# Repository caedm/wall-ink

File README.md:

# Introduction
Wall-ink was designed from the ground up to be a scalable, [secure](https://github.com/caedm/wall-ink/wiki/Device-security), and completely open solution to display conference room schedules at a university.  The product could, however, be developed to display other images for advertising, directions, staff directories, a weather station, retail pricing, etc.  Currently, the [wall-ink-server](https://github.com/caedm/wall-ink-server) can display schedules from the open source [Booked scheduler](https://www.bookedscheduler.com), any web published iCal file (Outlook / Exchange), and the Google Calendar API.  It can also [rotate through a collection of static images](https://github.com/caedm/wall-ink-server/wiki/Plugin-architecture#static-images-plugin).  With [additional development](https://github.com/caedm/wall-ink-server/wiki/Coding-a-new-plugin), other scheduler integrations or functions are possible.  The hardware simply displays whatever image it is given when it checks in with a wall-ink-server.  Development for putting images on the e-ink screen is made simpler by [allowing the image creation processing](https://github.com/caedm/wall-ink-server/wiki/Wall-ink-image-formats-and-image-handling) to occur on the server side, and not on the device.  Server-side image creation was a design choice for deploying a large fleet of these devices across mulitple buildings.  This way, changes can be made to what the devices are displaying without having to update firmware on dozens or hundreds of devices.  To date, we are aware of several other groups who have successfully written their own server-side software for wall-ink devices in various languages.  Links to other related wall-ink projects are found on the [additional wall ink projects](https://github.com/caedm/wall-ink/wiki/Additional-wall-ink-projects) page.

The original design parameters of this project were to display a room schedule electronically with no wires, at the cheapest possible price point.  No Ethernet, no power wires, in a low-cost footprint.  The resulting project has produced a AA powered WiFi E-ink device for under $100 (US), when parts are purchased in bulk, where the [batteries last a year or two](https://github.com/caedm/wall-ink/wiki/Circuit#batteries).  

The wall-ink project along with the [Wall-Ink-Server](https://github.com/caedm/wall-ink-server) includes everything necessary to build the entire e-ink display system. 

# Summary
The wall-ink project has several components:

* [Circuit and electronics](https://github.com/caedm/wall-ink/wiki/circuit), including Eagle schematic, PCB layout and gerber files
* List of necessary [parts](https://github.com/caedm/wall-ink/wiki/partslist) to build the project
* Arduino IDE [Firmware](https://github.com/caedm/wall-ink/wiki/firmware) for the ESP8266 microcontroller
* CAD files to 3D print the [Case](https://github.com/caedm/wall-ink/wiki/firmware)
* See the [Wall-Ink-Server](https://github.com/caedm/wall-ink-server) project for server side code

# FAQ

## What hardware does wall-ink run on and where do I get it?
The wall-ink project is a hardware, firmware, and software build.  To date, we are not aware of any off-the-shelf commercial products that will do everything that the [wall-ink device](https://github.com/caedm/wall-ink/wiki/7.5%22-Wall-ink-device) does.  There are plenty of ESP8266 devices out there, including ones that sleep, but the hardware as described here is specifically designed to run the wall-ink firmware, sleep, use very little power, fit in the supplied 3D printable case, and update a Waveshare e-ink screen.

## Can I hire you to make the hardware for me?
Due to conflict of interest policies at the University we work for, we are not available for hire to create hardware for you, or to customize software features for you.  That being said, we have uploaded all of the design files and code, and reasonable documentation to do it on your own.  Many people have created this project on their own with positive results.

## What is an ESP8266 and why did you choose that microprocessor?
The [ESP8266 by Espressif Systems](https://en.wikipedia.org/wiki/ESP8266) is similar to an Arduino, but has 10uA deep-sleep function and built-in WiFi with a full TCP/IP stack.  The ESP8266 is also low cost, and fully compatible with the Arduino IDE.  So for under $3, you get a microprocessor that is perfect for this project.

## Why e-ink?  Is it a touch display?
In order to run the device for over a year on a set of AA batteries, we needed to use the lowest power screen possible. Since e-ink screens can hold their image even with the power removed, this is by far the lowest power option out there.  To keep the cost down, the type of [E-ink screens](https://en.wikipedia.org/wiki/E-ink) we chose from Waveshare / Good Display does not have touch screen capability.

## What e-ink screens are supported?
The real limitation of screen resolution support is the RAM available on the esp8266.  Some server-side plugins like the static image plugin and the simple text plugin can handle any screen size dynamically.  Other plugins like the booked and google plugins that use the general scheduling functions are hard-coded for Waveshare 7.5" screens at 640x384 and Waveshare 4.2" screens at 400x300 pixels.  There is currently no support for color displays.  We believe that there would be insufficient memory to support the larger color screens using the current method that the firmware has been coded.  The color screens also take a significant amount of time to update, and the batteries would not last sufficiently long for our use-case, so we did not pursue this option.

## Why does a wall-ink device require a server?
Using a central server for controlling what is displayed on wall-ink devices was a design decision to ease the management of large numbers of devices.  If you only need to manage one e-ink device, running a server component might be overkill, but with dozens or hundreds of devices in the field, it is essential.  Tweaking what is being displayed on 100 or more screens can be done by changing a parameter on a website rather than updating firmware on dozens of devices across the enterprise.  Any wall-ink device pointed to a wall-ink-server can be configured do display ANY image at any time the next time in checks in.  There are also central management features such as looking at error logs, Nagios monitoring, voltage monitoring, and other such high-level tools, all made possible through this architecture.

## Can Wall-ink devices talk to a webserver using https?
The short answer is no.  There are libraries available for an esp8266 to talk to a webserver securely, but [there is not enough RAM onboard](https://github.com/caedm/wall-ink/wiki/Wall-ink-Memory#ram) to run the neccessary encryption code.  If security is a concern, please refer to the wiki articles about [device security](https://github.com/caedm/wall-ink/wiki/Device-security) and [wall-ink server security considerations](https://github.com/caedm/wall-ink-server/wiki/Security-considerations#image-security).

## Will a Wall-ink device connect to enterprise WiFi?
The short answer is maybe.  The ESP8266 WiFi client firmware has been tested to work with WPA2-PSK but does not appear to work with WPA2 Enterprise (including Eduroam). Some enterprises offer an additional "guest" network SSID with limited internal connectivity to handle embedded IOT devices as a solution to this problem.  Before going to the trouble of building this whole project and purchasing a screen, you could purchase an ESP8266 devkit and try connecting to your company's WiFi. 

## What skills and tools  will I need to complete this project?
Some basic electronics experience could be useful if building a [development board prototype](https://github.com/caedm/wall-ink/wiki/development-board-prototype). Building an actual [wall-ink device](https://github.com/caedm/wall-ink/wiki/wall-ink-device) will require some basic soldering and 3d printing, and some electronics experience would be useful to help identify and purchase all the right [parts](https://github.com/caedm/wall-ink/wiki/partslist). The software end of the project will require the use of the Arduino IDE to flash the firmware, and a simple web server to run the [wall-ink-server](https://github.com/caedm/wall-ink-server). The wall-ink-server project has only been tested with Apache, but should work with other server software that supports PHP.

# Getting started
To get a wall-ink device up and running, you will need to build a hardware device and flash it with the latest firmware.  Then you will need to install a [small web service] to host the content for your device to display.  Last, you will need to [configure your new hardware device](https://github.com/caedm/wall-ink/wiki/Admin-mode) to access your wireless network and find your webserver.
## Building the hardware
There are a couple different methods to get started with wall-ink hardware
### Option 1: 
Purchase an esp8266 development board, and a Waveshare e-ink display with HAT and make a [development board prototype](https://github.com/caedm/wall-ink/wiki/Development-board-prototype).  This method will get you up and running quickly with a minimal cost for a proof-of-concept project.  You will be able to power and flash the development board via USB from your computer.  These development boards are designed to be easy to use, but are not meant for battery operated production devices.  The integrated USB to serial chip on the development board alone will drain your batteries in a matter of days.  If you want your device to operate for years on end off of batteries, you will need to build the wall-ink circuit that has been specifically designed for low power draw.

### Option 2:  
Buy all the [loose parts](https://github.com/caedm/wall-ink/wiki/partslist) and solder them to the [printed circuit board](https://github.com/caedm/wall-ink/wiki/Printed-Circuit-Board).  You will also need to [3d print a case](https://github.com/caedm/wall-ink/wiki/7.5%22-Wall-ink-case) for the project.  If you want to start with the real thing, there is no reason why you can't just go straight to it.

## Building and flashing the firmware on to the ESP8266
See the detailed instructions in the [building and flashing firmware wiki article](https://github.com/caedm/wall-ink/wiki/firmware#Building) for instructions on uploading the firmware.

## Install and configure the web server code
See the documentation for the [wall-ink-server](https://github.com/caedm/wall-ink-server) companion project.  If desired, you could write a much simpler server that was not designed for an enterprise as long as it returned files in the correct ["wink format"](https://github.com/caedm/wall-ink-server/wiki/Wall-ink-image-formats-and-image-handling#wink-file-format).  The wall-ink-server project is designed to handle hundreds of devices using various plugins to collect data and present images to the screens.  It includes Nagios monitoring scripts, battery monitors and other tools to handle a large fleet of wall-ink devices.
## Configure the device
Use [Admin mode](https://github.com/caedm/wall-ink/wiki/Admin-mode) to set up the wireless client, the image key, and the URL to get images from.

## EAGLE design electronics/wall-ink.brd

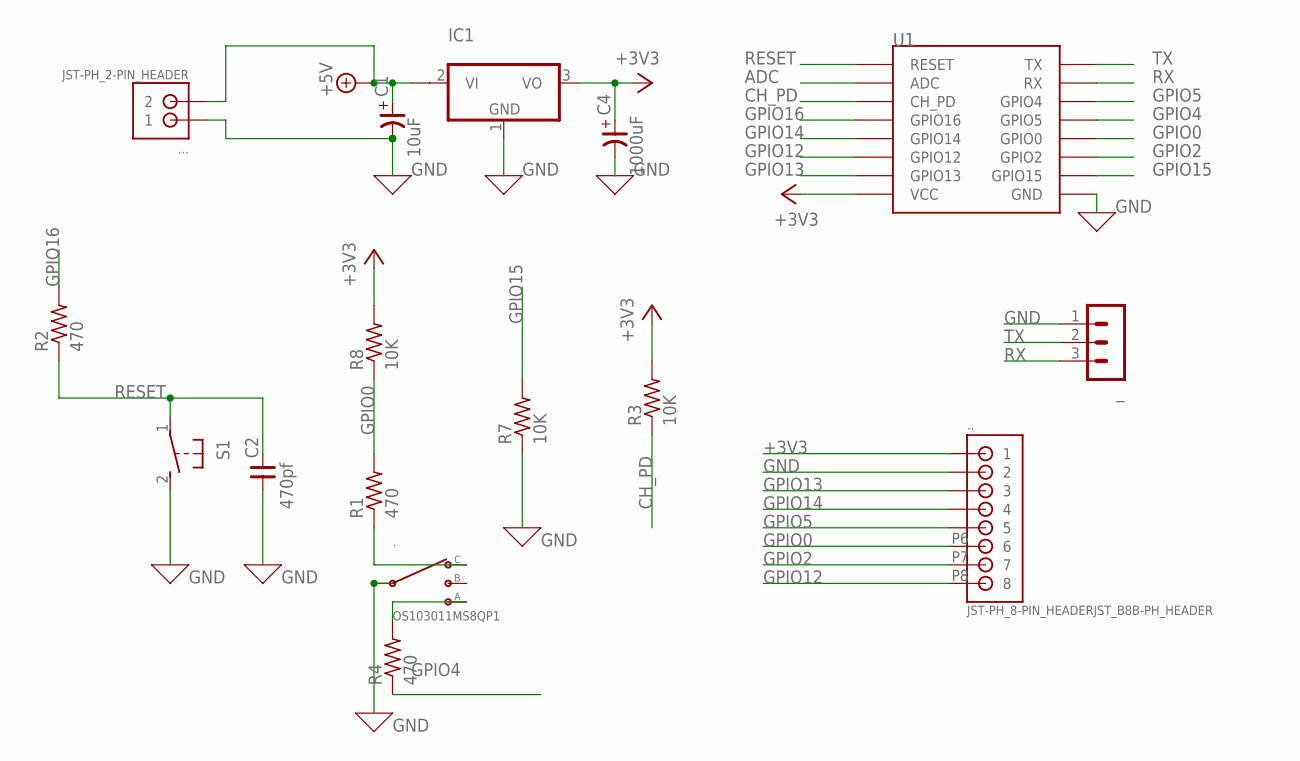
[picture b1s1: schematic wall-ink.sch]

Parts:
.: OS103011MS8QP1; OS102011MS8QP1
..: JST-PH_8-PIN_HEADERJST_B8B-PH_HEADER; JST_B5B-PH_HEADER
...: JST-PH_2-PIN_HEADER; JST_B2B-PH_HEADER
C1: 10uF; E-020X050
C2: 470pf; C025-040X018
C4: 1000uF; E-050X100
IC1: MCP170312MB; SOT89
R1, R2, R4: 470; 0204/5
R3, R7, R8: 10K; 0204/5
S1: 31-XX; B3F-31XX
U1: ESP12SMD; ESP12-SMD
_: MA03-1

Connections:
+3V3: ...P1 (1), C4.+, IC1.3 (VO), R3.2, R8.2, U1.VCC
+5V: ....P2 (2), C1.+, IC1.2@1 (VI1)
ADC: U1.ADC
CH_PD: R3.1, U1.CH_PD
GND: ..2 (C), ...P2 (2), ....P1 (1), C1.-, C2.1, C4.-, IC1.1 (GND), R7.1, S1.2 (S), U1.GND, _.1
GPIO0: ...P6 (6), R1.2, R8.1, U1.GPIO0
GPIO2: ...P7 (7), U1.GPIO2
GPIO4: R4.1, U1.GPIO5
GPIO5: ...P5 (5), U1.GPIO4
GPIO12: ...P8 (8), U1.GPIO12
GPIO13: ...P3 (3), U1.GPIO13
GPIO14: ...P4 (4), U1.GPIO14
GPIO15: R7.2, U1.GPIO15
GPIO16: R2.2, U1.GPIO16
unnamed: ..4 (3), R1.1
unnamed: ..1, R4.2
RESET: C2.2, R2.1, S1.1, U1.RESET
RX: U1.RXD0 (RX), _.3
TX: U1.TXD0 (TX), _.2

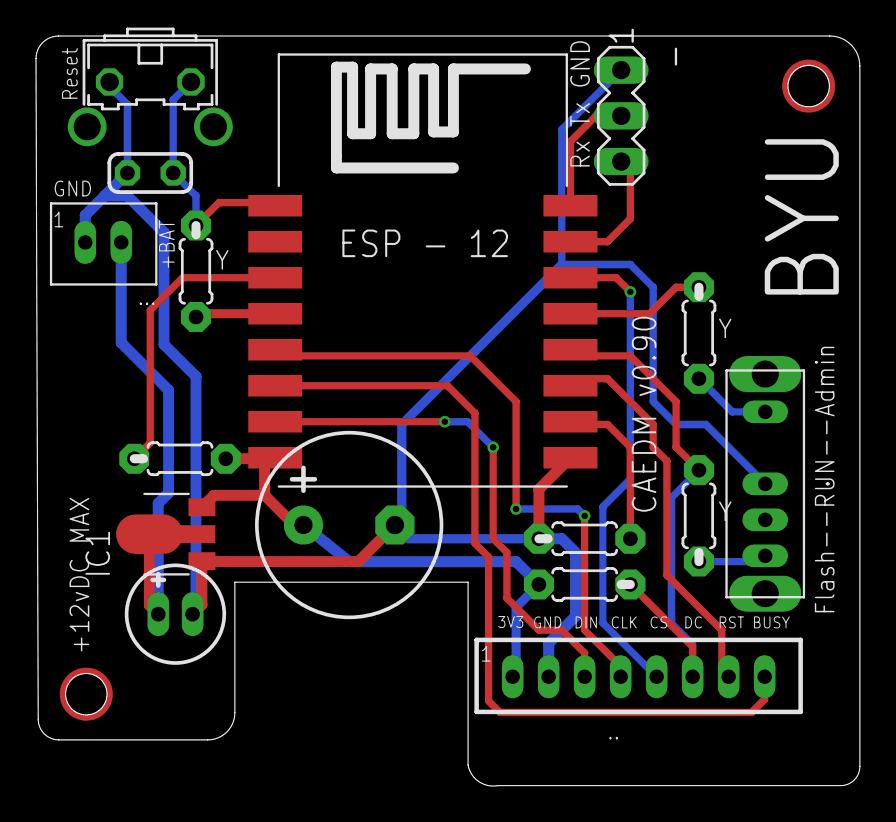
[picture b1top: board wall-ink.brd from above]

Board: 2 copper layers, 45.8 x 41.7 mm, 16 parts (0 on the bottom side), 18 nets.

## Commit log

2017-12-01 Initial commit. Things work.
2017-12-14 Added support for different screen configurations
2017-12-15 fixed a bug with debug code, now ignores the first 8 bytes (these are time information)
2017-12-15 Downloads sleep time from server and splits sleep into 30 minute segments
2017-12-19 Added some debug code, changed the way the esp8266 queries the server
2017-12-19 Added code to handle crashes
2017-12-19 Added some debug info, the URL is now autogenerated from the device's MAC address.
2018-01-08 Added some debug output, started to cahnge how WiFi connections are made
2018-01-08 RTC memory is now handled sanely.
2018-01-08 WiFi channel and BSSID now saved in RTC memory
2018-01-08 Don't write wifi info to flash
2018-01-08 Added note on board version
2018-01-09 WiFi should(?) go to some sort of lower-power state before screen is flashed now
2018-01-12 Added support for multiple wifi profiles, added debug stuff
2018-01-12 fixed bug with randomized seed
2018-01-12 removed erroneous debug message
2018-01-18 changed wifi code to fail on bad connection
2018-01-24 device should now crash if image is an empty file
2018-02-09 Fixed a bug relating to time drift and static images
2018-02-09 Only the black pixels from a given image get written now, saving 600ms for the 7" screen
2018-03-09 Fixed a mysterious wifi bug relating to how WiFiMulti.run() was being called
2018-03-22 The debug build now points to the test server
2018-03-22 Changed the threshhold for a wifi connection to be considered weak
2018-05-29 Added security, fixed a problem in the decompression algorithm
2018-06-11 CS pin on the screen is now connected to GPIO5
2018-06-14 Added basic support for WiFi configuration
2018-06-15 Debug is now set online; mac address is broadcasted as part of the ssid
2018-06-18 fixed a bug with the debug code change, form fields should autopopulate now.
2018-06-18 There should now be an indicator at the bottom of the screen when debug mode is active
2018-06-18 The debug indicator mentioned in the previous commit now works
2018-06-18 The RTC info is now invalidated whenever anything is written to the eeprom.
2018-06-19 That thing from the previous commit works now
2018-06-19 Added more information to be displayed to the screen while debug mode is active
2018-06-20 Added a wifi password to admin mode, added a screen with instructions to admin mode
2018-06-21 Dean fixed a bug that would sometimes cause the screens to not load an image
2018-06-21 RTC memory is now invalidated whenever admin mode is activated
2018-06-21 The device no longer displays information when it initially boots
2018-06-21 The device doesn't wait as long to throw errors to the screen as it did before
2018-06-21 The admin mode image now includes a QR code to get tothe web managment console
2018-06-21 It builds now
2018-06-21 Moved the QR code on the admin screen
2018-06-22 Added slightly more information to admin mode's web interface
2018-06-22 Commited something I guess I forgot to commit
2018-06-22 Added GPLv3 license text
2018-06-27 Added a couple of yield commands, added extremely basic error reporting
2018-06-27 Fixed a problem where rtcData.numErrors may not have been initialized
2018-06-27 The admin mode github url is now correct
2018-06-28 Changed how errors are reported, added a key for error codes
2018-06-28 Fixed some dumb bugs
2018-07-05 Update readme.md
    First draft of readme
2018-07-05 Further update of readme.md
    Added 5 more sections to the readme.md
2018-07-05 updated readme.md to fix formatting error
2018-07-05 Updated links to wiki
2018-07-09 Added PCB eagle schematic, board, and gerber files
2018-07-09 Added CAD files for the case
2018-07-10 Added the CAD files for the faceplate
2018-07-10 Added pictures for use in wiki
2018-07-10 The default values for SSIDs and passwords are once again settable in define statements at the top
2018-07-10 Deleted some photos we don't actually want any more
2018-07-13 Updated readme with a diagram
2018-07-27 Modified case to better fit the faceplate
2018-07-27 Added a 20 byte security hash at the beginning of each file. Compatible with commit 71cd99d of the server software & up.
2018-07-27 Fixed a bug in the previous version that was causing the devices to sleep for a decade at a time
2018-08-09 Changed some error messages
2018-09-13 Added a timer so the device won't stay in admin mode indefinitely
2018-09-27 fixed typo
2018-10-08 Fix broken link to admin mode
2018-10-30 Fixed an image decompression bug that would occur in certain edge cases
2018-11-02 put credentials in a separate file
2018-11-02 added gitignore
2018-11-02 Removed compression because there was a bug that was causing issues
2018-11-13 Wall-Ink devices now report their screen resolution in the HTTP GET request
2018-11-19 Fixed a bug that was causing error logging to not work
2018-11-21 Fixed issue 4, next attempt seconds should be accurate now.
2018-11-21 changed the amount of time before a screen starts outwardly displaying errors from 20 minutes back to 80 minutes
2018-11-21 Fixed some typos
2018-11-29 Added basic protection against message replay attacks. More thorough protection will be added in a future update.
2018-12-03 Added additional protections against certain types of replay attacks. Compatible with commit f995e454 of wall-ink-server.
2018-12-06 Fixed some bugs relating to failed wifi connections and error handling
2019-01-10 Fixed an issue where the device would sometimes go into AP_STA mode instead of STA mode
2019-01-11 Admin mode should work for 4" screens now
2019-01-11 Made a small change so that the last commit now works
2019-01-20 Styled the Admin Screen for an easier configuration of the device
    Beside the styling the importand part was to add a MAC Address copy to clipboard functionality, which makes it easier to configure the device on the server
2019-01-22 Incremented version number to represent improved UI from koos
2019-01-28 issue 17: changed the amount of time that the device sleeps for when an error occurs
2019-01-28 Added some reinforcement to the case
2019-01-28 Removed our server's url from the code, formatted whitespace in a more unified way
2019-04-15 issue 20: modified case design for new HATs
2019-04-19 issue 20: added adaptor to use new HATs in old cases
